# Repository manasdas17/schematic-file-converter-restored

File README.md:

**WARNING:  Upverter is in the process of overhauling our UPV format to a new version.  We don't expect to maintain the current version, however we look forward to sharing our new version with you when it's ready to go!**

The Upverter Universal Format Converter
=======================================
A command line python anything-in anything-out file converter to go between the multitude of electrical circuit schematic file formats. This project was started by Upverter (http://upverter.com).

Folder Contents
---------------

* `upconvert/core/` - All of the converter code
* `doc/` - Everything related to documentation
* `upconvert/library/` - Library files for the software packages that dont export complete files
* `upconvert/parser/` - All of the in code
* `test/` - A set of test files for each format
* `upconvert/writer/` - All of the out code

Usage
---------------

```bash
usage: python2 -m upconvert.upconverter [-h] [-i INPUT] [-f TYPE] [-o OUTPUT] [-s SYMDIRS [SYMDIRS ...]] [-t TYPE]

optional arguments:
  -h, --help            show this help message and exit

  -i INPUT, --input INPUT
                        read INPUT file in
  -f TYPE, --from TYPE  read input file as TYPE

  -o OUTPUT, --output OUTPUT
                        write OUTPUT file out
  -t TYPE, --to TYPE    write output file as TYPE

  -s SYMDIRS [SYMDIRS ...], --sym-dirs SYMDIRS [SYMDIRS ...]
                        specify SYMDIRS to search for .sym files (for gEDA
                        only)

  --unsupported         run with an unsupported python version
  --raise-errors        show tracebacks for parsing and writing errors
  --profile             collect profiling information
  -v, --version         print version information and quit
  --formats             print supported formats and quit
```

Where to Get Help
---------------

```bash
python2 -m upconvert.upconverter -h
```

  Github: Submit an issue, or pull request.
  Email: support@upverter.com

Supported Formats
---------------

  The converter can import and export in the following popular open and closed source formats.

* Upverter OpenJSON
* KiCad
* gEDA
* Fritzing
* RS274-X Gerber (see note)
* NC Drill
* Eagle
* Eagle XML             (in testing)
* ViewDraw / DxDesigner (in testing)
* DSN                   (in testing)
* PNG Image
* Bill of Materials
* CSV Netlist
* Altium                (in development)
* Telesis Netlist       (in development)

Gerber Export Note:
Gerber export requires the arial.ttf font in the working directory the converter is run from.

Format Wish List
---------------

  This is the list of formats we wish we supported, and will work on or finish someday soon. We are looking for developers to help us so please ping us if you're interested!

* OrCad
* Existing supported formats - layout data
* DipTrace

The Concept
---------------

  To use an Upverter Open JSON export in another piece of software, you will need to convert it into that software's proprietary format. Likewise, to get your data out of another piece of software and import it into Upverter, you will also need to run their export through the converter. We are working to make this easier, but we will largely depend on community contribution and the participation of the other vendors.

Interchange Format Documentation
---------------

  The converter is based on the Upverter Open JSON Format fully documented at http://support.upverter.com/customer/portal/articles/553504-documentation-for-open-json-format. We hope that someday all of the major providers of schematic capture software will support interoperability with open formats like this one.

Key Contributors
---------------

  The converter has been an ongoing project since mid-2011 made up of many, many contributions by a team of distributed developers associated by little more than our desire to fix what we see as the horribly broken world of ECAD interoperability. The key contributors are as follows:

* jdavisp3    -  KiCad, Fritzing, EagleXML, Stability
* elbaschid   -  gEDA
* iparshin    -  EagleBin
* foobarmus   -  Gerber
* patrickyeon -  ViewDraw, Image
* machinaut   -  OpenJSON, Architecture

Licence
---------------

  http://www.apache.org/licenses/LICENSE-2.0.html

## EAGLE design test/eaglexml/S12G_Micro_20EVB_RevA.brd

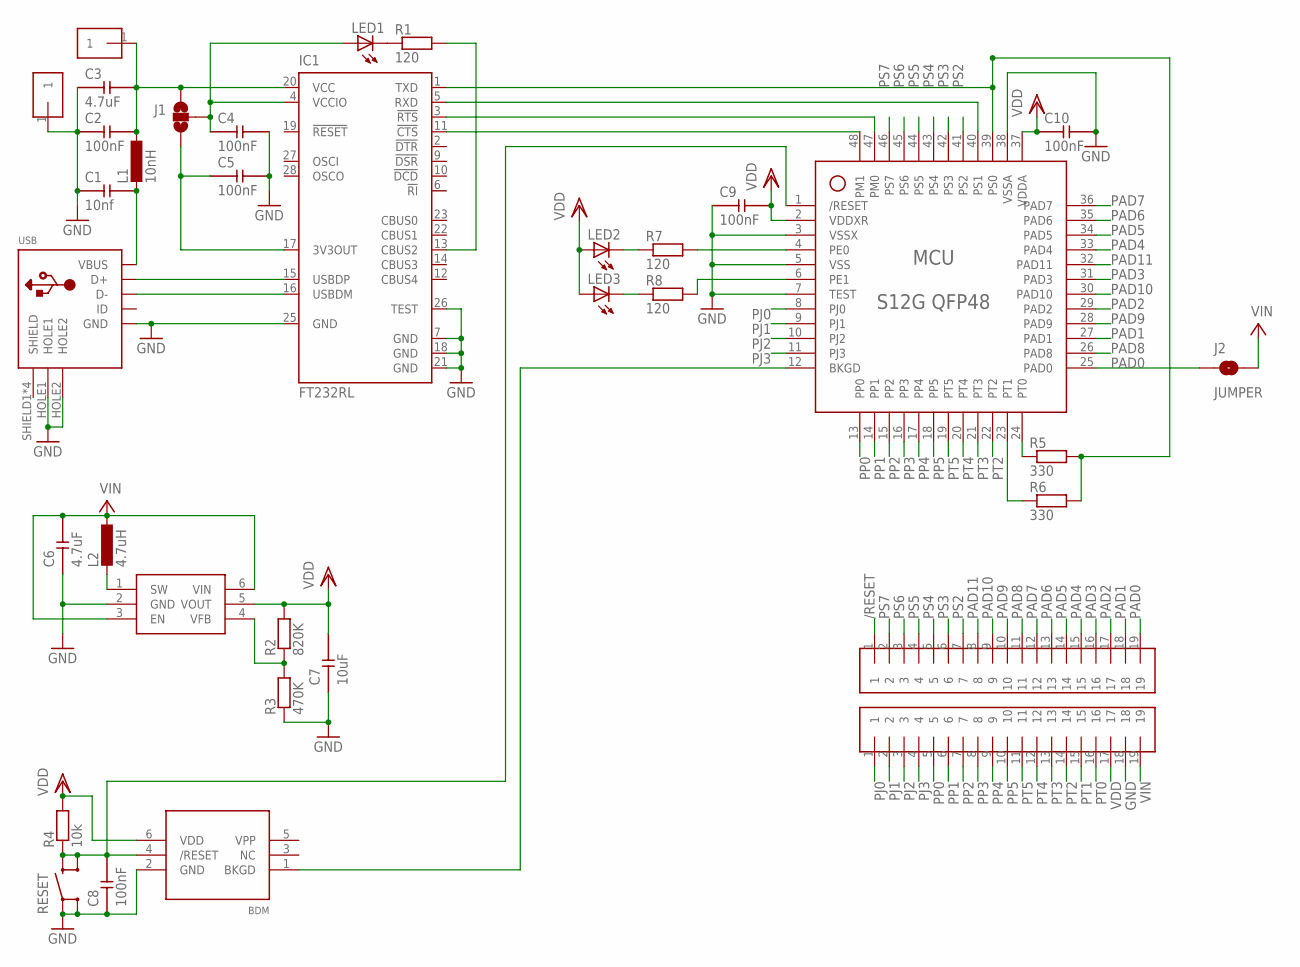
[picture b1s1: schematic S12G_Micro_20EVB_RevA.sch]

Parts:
BDM: BDM
BOTTOM: 1X19
C1: 10nf; 0805
C2, C4, C5, C8, C9, C10: 100nF; 0805
C3, C6: 4.7uF; 0805
C7: 10uF; 0805
GND: 1X1
IC1: FT232RL; SSOP28
IC2: MCP1640; SOT23-6
J1: JUMPER_2WAY
J2: JUMPER
L1: 10nH; 0805
L2: 4.7uH; LQH3C@1
LED1, LED2, LED3: LED0805; 0805
MCU: S12G QFP48; QFP44
R1, R7, R8: 120; 0805
R2: 820K; 0805
R3: 470K; 0805
R4: 10k; 0805
R5, R6: 330; 0805
RESET: BUTTON
TOP: 1X19
USB: USB; USB_MINI_B
VUSB: 1X1

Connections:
3V3OUT: C5.2, IC1.17 (3V3OUT), J1.3
/RESET: BDM.4 (/RESET), C8.1, MCU.1 (/RESET), R4.2, RESET.2, RESET.4, TOP.1
BKGD: BDM.1 (BKGD), MCU.12 (BKGD)
CTS: IC1.11 (!CTS), MCU.48 (PM1)
GND: BDM.2 (GND), BOTTOM.18, C1.2, C2.2, C3.2, C4.1, C5.1, C6.2, C7.2, C8.2, C9.2, C10.1, GND.1, IC1.7 (GND), IC1.18 (GND), IC1.21 (GND), IC1.25 (GND), IC1.26 (TEST), IC2.2 (GND), MCU.3 (VSSX), MCU.5 (VSS), MCU.7 (TEST), MCU.38 (VSSA), R3.2, RESET.1, RESET.3, USB.GND, USB.HOLE1, USB.HOLE2
unnamed: LED3.2 (C), R8.2
unnamed: IC2.4 (VFB), R2.2, R3.1
unnamed: LED2.2 (C), R7.2
unnamed: LED1.2 (C), R1.2
unnamed: IC1.13 (CBUS2), R1.1
unnamed: IC2.1 (SW), L2.3 (2), L2.4 (2)
PAD0: J2.1, MCU.25 (PAD0), TOP.19
PAD1: MCU.27 (PAD1), TOP.18
PAD2: MCU.29 (PAD2), TOP.17
PAD3: MCU.31 (PAD3), TOP.16
PAD4: MCU.33 (PAD4), TOP.15
PAD5: MCU.34 (PAD5), TOP.14
PAD6: MCU.35 (PAD6), TOP.13
PAD7: MCU.36 (PAD7), TOP.12
PAD8: MCU.26 (PAD8), TOP.11
PAD9: MCU.28 (PAD9), TOP.10
PAD10: MCU.30 (PAD10), TOP.9
PAD11: MCU.32 (PAD11), TOP.8
PE0: MCU.4 (PE0), R7.1
PE1: MCU.6 (PE1), R8.1
PJ0: BOTTOM.1, MCU.8 (PJ0)
PJ1: BOTTOM.2, MCU.9 (PJ1)
PJ2: BOTTOM.3, MCU.10 (PJ2)
PJ3: BOTTOM.4, MCU.11 (PJ3)
PP0: BOTTOM.5, MCU.13 (PP0)
PP1: BOTTOM.6, MCU.14 (PP1)
PP2: BOTTOM.7, MCU.15 (PP2)
PP3: BOTTOM.8, MCU.16 (PP3)
PP4: BOTTOM.9, MCU.17 (PP4)
PP5: BOTTOM.10, MCU.18 (PP5)
PS2: MCU.41 (PS2), TOP.7
PS3: MCU.42 (PS3), TOP.6
PS4: MCU.43 (PS4), TOP.5
PS5: MCU.44 (PS5), TOP.4
PS6: MCU.45 (PS6), TOP.3
PS7: MCU.46 (PS7), TOP.2
PT0: BOTTOM.16, MCU.24 (PT0), R5.2
PT1: BOTTOM.15, MCU.23 (PT1), R6.2
PT2: BOTTOM.14, MCU.22 (PT2)
PT3: BOTTOM.13, MCU.21 (PT3)
PT4: BOTTOM.12, MCU.20 (PT4)
PT5: BOTTOM.11, MCU.19 (PT5)
RTS: IC1.3 (!RTS), MCU.47 (PM0)
RXD: IC1.1 (TXD), MCU.39 (PS0), R5.1, R6.1
SHIELD: USB.SHIELD1 (SHIELD), USB.SHIELD2 (SHIELD), USB.SHIELD3 (SHIELD), USB.SHIELD4 (SHIELD)
TXD: IC1.5 (RXD), MCU.40 (PS1)
USBDN: IC1.16 (USBDM), USB.D-
USBDP: IC1.15 (USBDP), USB.D+
VBUS: C1.1, L1.2, USB.VBUS
VCCIO: C4.2, IC1.4 (VCCIO), J1.2, LED1.1 (A)
VDD: BDM.6 (VDD), BOTTOM.17, C7.1, C9.1, C10.2, IC2.5 (VOUT), LED2.1 (A), LED3.1 (A), MCU.2 (VDDXR), MCU.37 (VDDA), R2.1, R4.1
VDDUSB: C2.1, C3.1, IC1.20 (VCC), J1.1, L1.1, VUSB.1
VIN: BOTTOM.19, C6.1, IC2.3 (EN), IC2.6 (VIN), J2.2, L2.1, L2.5 (1)

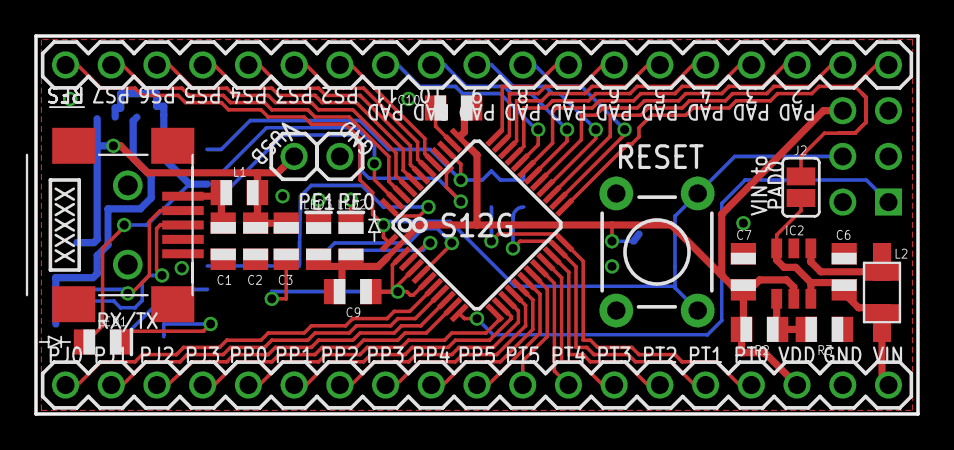
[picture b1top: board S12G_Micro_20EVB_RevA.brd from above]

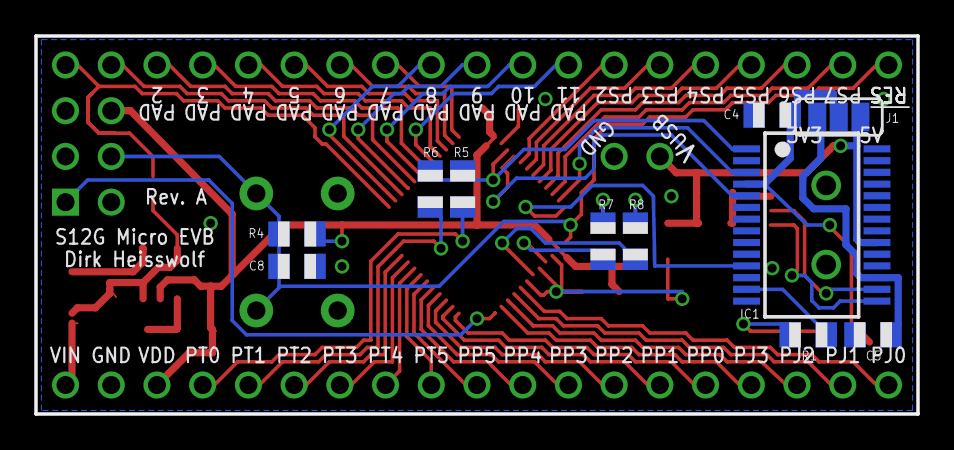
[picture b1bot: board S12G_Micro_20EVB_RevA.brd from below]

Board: 2 copper layers, 49.0 x 21.0 mm, 35 parts (11 on the bottom side), 58 nets.

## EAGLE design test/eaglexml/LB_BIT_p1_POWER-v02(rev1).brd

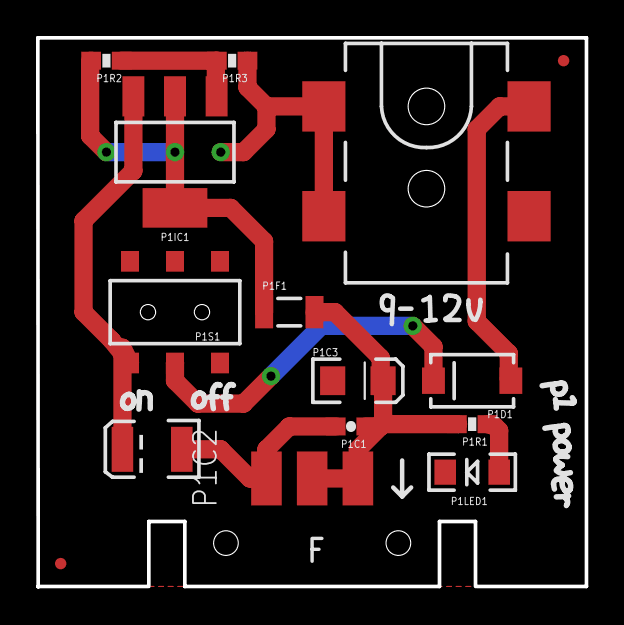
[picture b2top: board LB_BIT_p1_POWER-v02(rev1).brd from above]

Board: 2 copper layers, 30.5 x 30.5 mm, 18 parts (0 on the bottom side), 8 nets.

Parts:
JP1, JP2: FIDUCIAL1X2.5; FIDUCIAL-1X2.5
P1BSF: BITSNAP_FEMALE
P1C1: 0.1uF; 0603-CAP
P1C2: 10uF/20V; EIA3528
P1C3: 10uF; EIA3216
P1D1: MBRA140; SMA-DIODE
P1F1: 500mA PTC; PTC-1206
P1IC1: SOT223
P1J1: POWER_JACKSMD; POWER_JACK_SMD
P1LED1: RED; LED-1206
P1R1: 330; 0603-RES
P1R2: 240; 0603-RES
P1R3: 720; 0603-RES
P1S1: AYZ0202
U$1: LB_CREDITS; OSHWCREDIT
U$2: OSHW_FILLX150_NOTEXT
U$3: OSHW-LOGOL; OSHW-LOGO-L

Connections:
GND: P1BSF.GND, P1C1.2, P1C2.C, P1C3.C, P1J1.GND, P1J1.P$4, P1LED1.C, P1R3.1
unnamed: P1D1.C, P1S1.2
unnamed: P1F1.1, P1IC1.2, P1IC1.4, P1R2.2
unnamed: P1IC1.1, P1R2.1, P1R3.2
unnamed: P1C2.A, P1IC1.3, P1S1.3
unnamed: P1D1.A, P1J1.VIN0
unnamed: P1LED1.A, P1R1.1
VCC: P1BSF.SIG, P1BSF.VCC, P1C1.1, P1C3.A, P1F1.2, P1R1.2

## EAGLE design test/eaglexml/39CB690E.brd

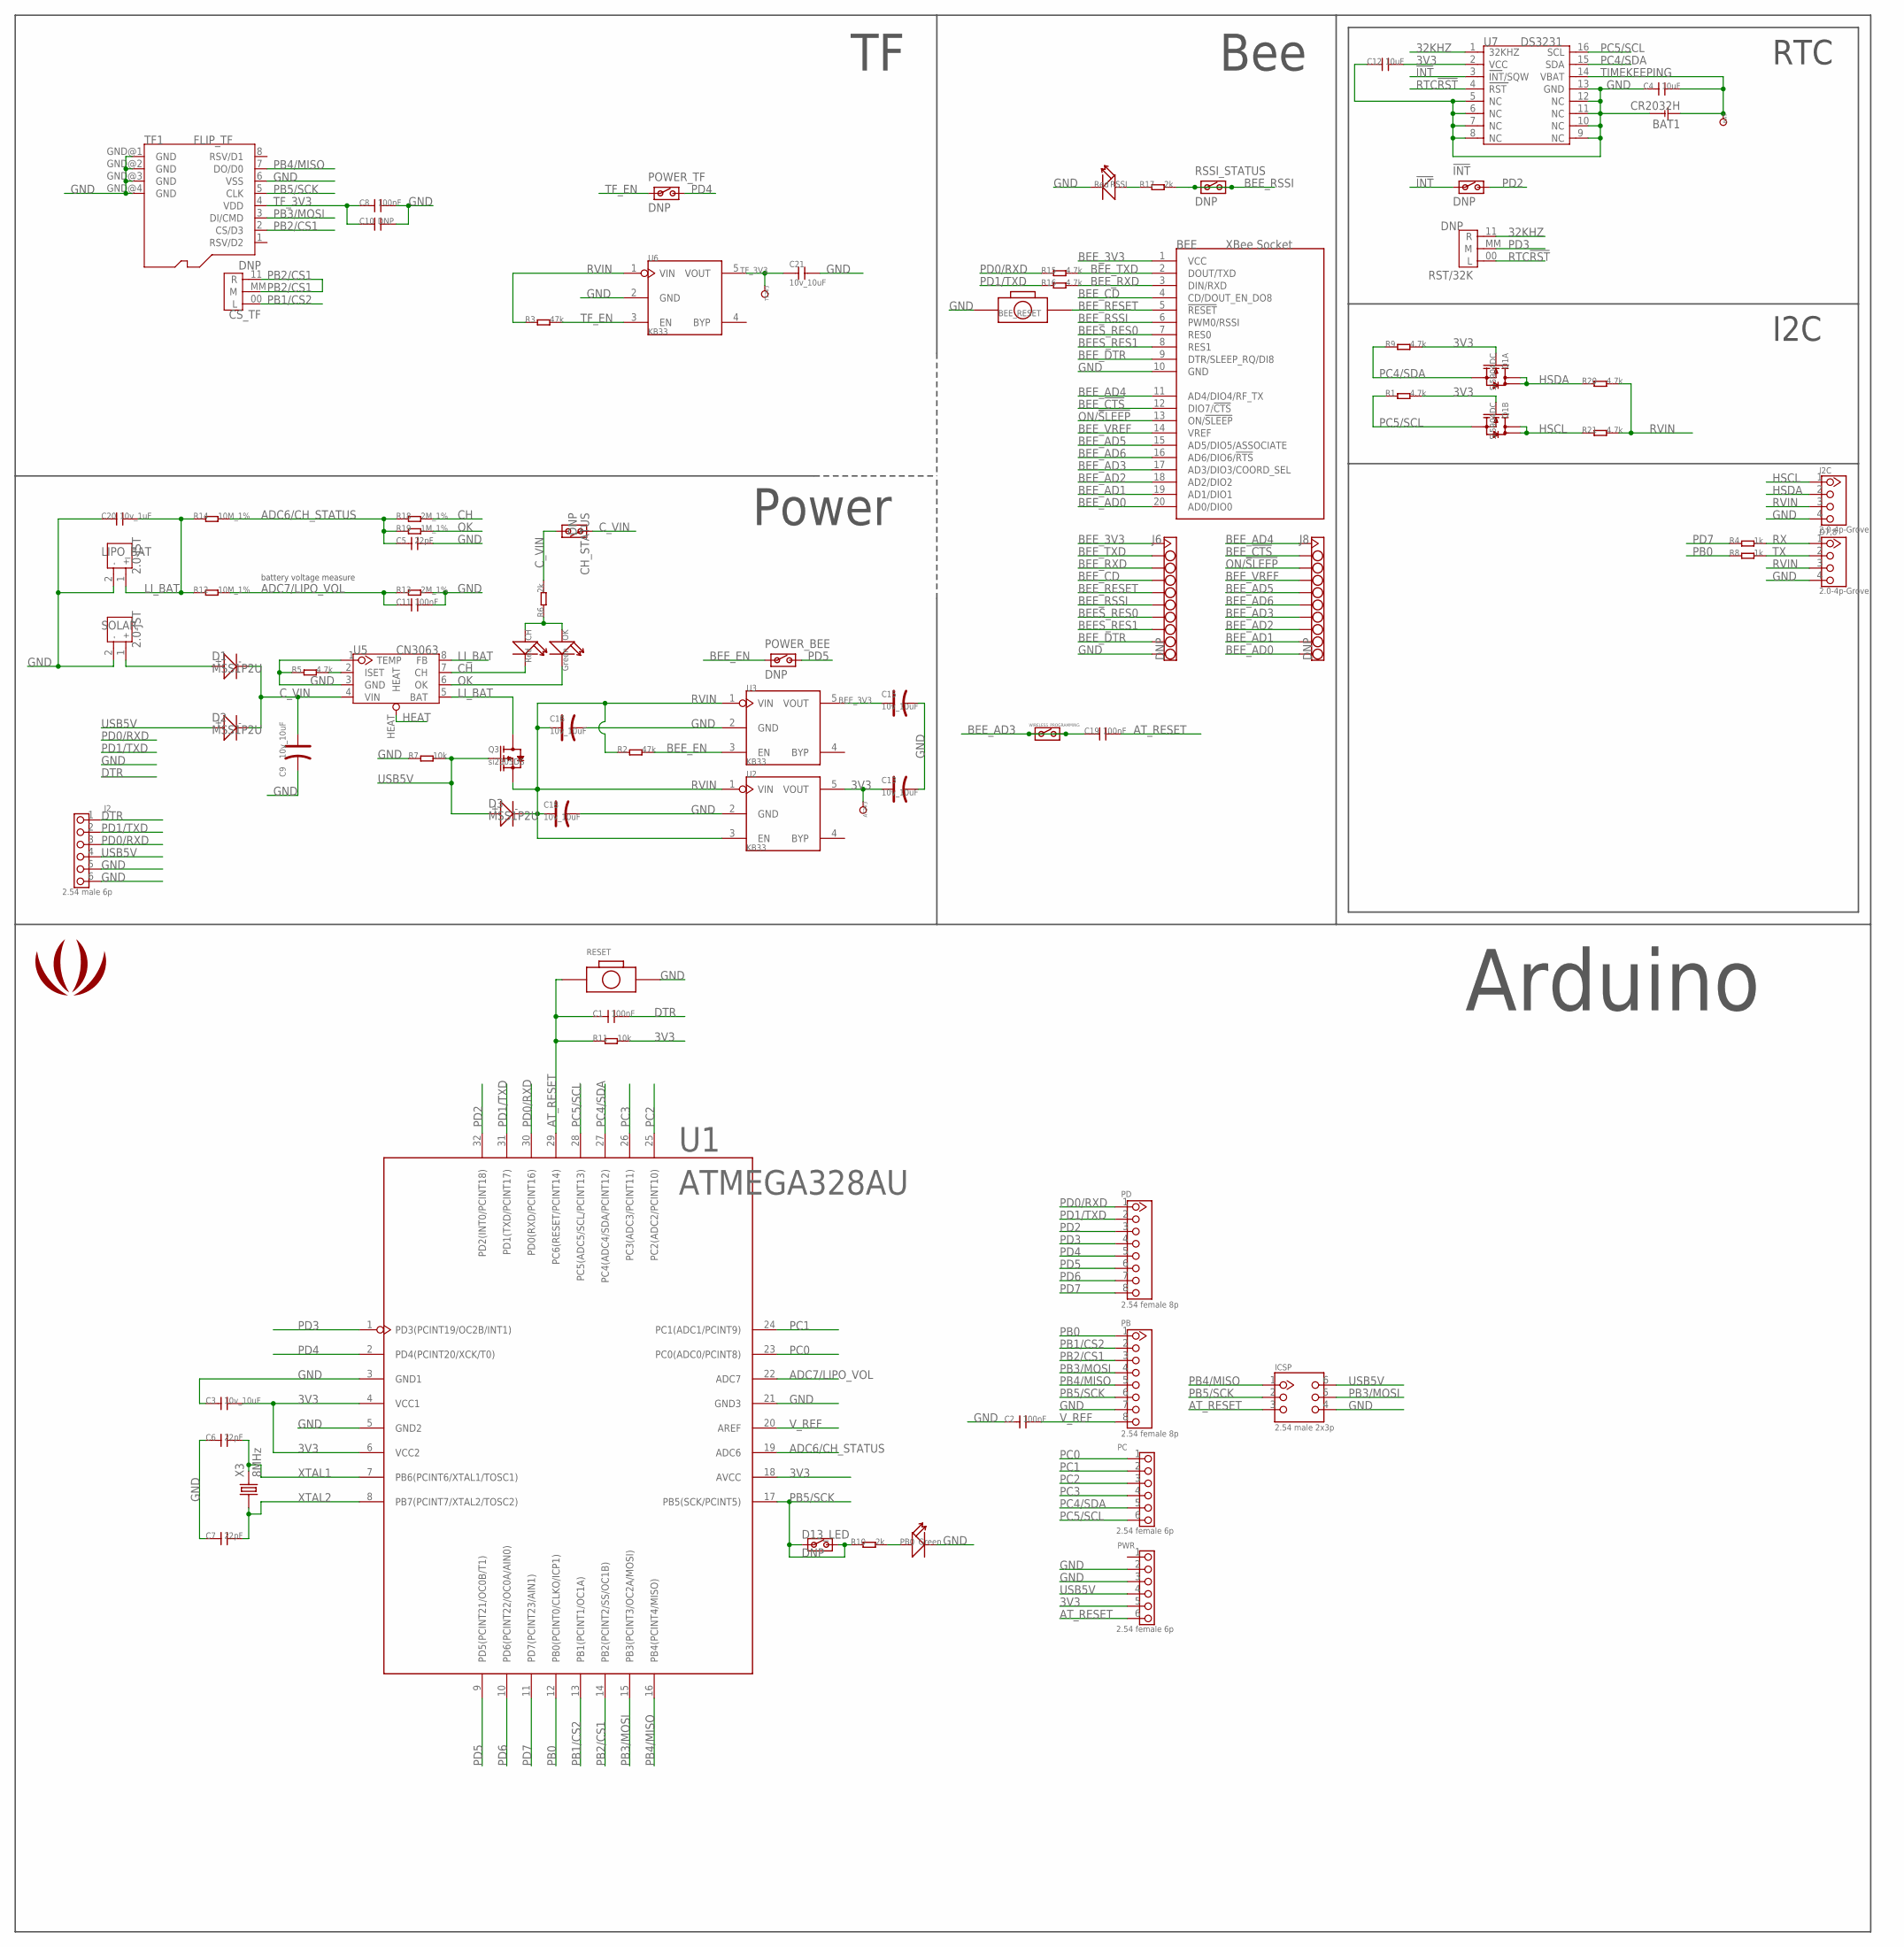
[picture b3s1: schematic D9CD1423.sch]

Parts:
!INT: DNP; JP_SW
AT3V3: DNP; TP_3535
BAT: DNP; TP_3535
BAT1: CR2032H
BEE: XBee Socket; BEE
BEE_RESET: 3.8x6.1 button; BOTTON_1
C1, C2, C8, C11, C19: 100nF; 0603
C3, C21: 10v_10uF; 0805
C4, C12: 10uF; 0805
C5, C6, C7: 22pF; 0603
C9, C13, C15, C16, C18: 10v_10uF; AVX-A
C10: DNP; 0603
C20: 10v_1uF; 0805
CH: Red; D0603
CH_STATUS: DNP; JP_SW
CS_TF: DNP; JUMPER
D1, D2, D3: MSS1P2U; D1005
D7,8: 2.0-4p-Grove; 4P-2.0
D13_LED: DNP; JP_SW
I2C: 2.0-4p-Grove; 4P-2.0
ICSP: 2.54 male 2x3p; 2X3P-2.54-LEADED
J2: 2.54 male 6p; 6P-2.54-LEADED
J6, J8: DNP; HEADER_1X10
LIPO_BAT: 2.0-JST; JST-2.0
LOGO1: LOGO; LOGO_RO
OK: Green; D0603
PB: 2.54 female 8p; 8P-2.54-LEADED
PB0: Green; D0603
PC: 2.54 female 6p; 6P-2.54-LEADED
PD: 2.54 female 8p; 8P-2.54-LEADED
POWER_BEE: DNP; JP_SW
POWER_TF: DNP; JP_SW
PWR: 2.54 female 6p; 6P-2.54-LEADED
Q1: Si5904DC; 1206-8
Q3: si2305DS; SOT23
R1, R5, R9, R15, R16, R20, R21: 4.7k; 0603@1
R2, R3: 47k; 0603@1
R4, R8: 1k; 0603@1
R6, R10, R17: 2k; 0603@1
R7, R11: 10k; 0603@1
R12, R14: 10M_1%; 0603@1
R13, R18: 2M_1%; 0603@1
R19: 1M_1%; 0603@1
RESET: 3.8x6.1 button; BOTTON_1
RSSI: Red; D0603
RSSI_STATUS: DNP; JP_SW
RST/32K: DNP; JUMPER
SOLAR: 2.0-JST; JST-2.0
TF1: FLIP_TF
TF3V3: DNP; TP_3535
U1: ATMEGA328AU; ATMEGA168-20AU
U2, U3, U6: KB33; SOT23-5
U5: CN3063; SOP8
U7: DS3231; SO16-W
WIRELESS_PROGRAMMING: DNP; JP_SW
X3: 8MHz; HC49/S

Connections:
3V3: AT3V3.T, C3.2, C12.2, C13.+, PWR.5, Q1.2 (G), Q1.4 (G), R1.2, R9.2, R11.2, U1.4 (VCC1), U1.6 (VCC2), U1.18 (AVCC), U2.5 (VOUT), U7.2 (VCC)
32KHZ: RST/32K.11 (R), U7.1 (32KHZ)
!INT: !INT.1, U7.3 (INT/SQW)
ADC6/CH_STATUS: C5.1, R14.2, R18.1, R19.1, U1.19 (ADC6)
ADC7/LIPO_VOL: C11.1, R12.2, R13.1, U1.22 (ADC7)
AT_RESET: C1.1, C19.2, ICSP.3, PWR.6, R11.1, RESET.1, U1.29 (PC6(RESET/PCINT14))
BEES_RES0: BEE.7 (RES0), J6.7
BEES_RES1: BEE.8 (RES1), J6.8
BEE_3V3: BEE.1 (VCC), C15.+, J6.1, U3.5 (VOUT)
BEE_!CTS: BEE.12 (DIO7/!CTS), J8.2
BEE_AD0: BEE.20 (AD0/DIO0), J8.10
BEE_AD1: BEE.19 (AD1/DIO1), J8.9
BEE_AD2: BEE.18 (AD2/DIO2), J8.8
BEE_AD3: BEE.17 (AD3/DIO3/COORD_SEL), C19.1, J8.7, WIRELESS_PROGRAMMING.1, WIRELESS_PROGRAMMING.2
BEE_AD4: BEE.11 (AD4/DIO4/RF_TX), J8.1
BEE_AD5: BEE.15 (AD5/DIO5/ASSOCIATE), J8.5
BEE_AD6: BEE.16 (AD6/DIO6/!RTS), J8.6
BEE_CD: BEE.4 (CD/DOUT_EN_DO8), J6.4
BEE_DTR: BEE.9 (DTR/SLEEP_RQ/DI8), J6.9
BEE_EN: POWER_BEE.1, R2.2, U3.3 (EN)
BEE_RESET: BEE.5 (!RESET), BEE_RESET.P$2 (2), J6.5
BEE_RSSI: BEE.6 (PWM0/RSSI), J6.6, R17.2, RSSI_STATUS.1, RSSI_STATUS.2
BEE_RXD: BEE.3 (DIN/RXD), J6.3, R16.2
BEE_TXD: BEE.2 (DOUT/TXD), J6.2, R15.2
BEE_VREF: BEE.14 (VREF), J8.4
CH: CH.-, R18.2, U5.7 (CH)
C_VIN: C9.+, CH_STATUS.1, CH_STATUS.2, D1.-, D2.-, R6.2, U5.4 (VIN)
DTR: C1.2, J2.1
GND: BAT1.-, BEE.10 (GND), BEE_RESET.1, C2.1, C3.1, C4.1, C5.2, C6.1, C7.1, C8.2, C9.-, C10.2, C11.2, C12.1, C13.-, C15.-, C16.-, C18.-, C20.1, C21.2, D7,8.4, I2C.4, ICSP.4, J2.5, J2.6, J6.10, LIPO_BAT.2, PB.7, PB0.-, PWR.2, PWR.3, R5.1, R7.1, R13.2, RESET.P$2 (2), RSSI.-, SOLAR.2, TF1.6 (VSS), TF1.GND@1 (GND), TF1.GND@2 (GND), TF1.GND@3 (GND), TF1.GND@4 (GND), U1.3 (GND1), U1.5 (GND2), U1.21 (GND3), U2.2 (GND), U3.2 (GND), U5.1 (TEMP), U5.3 (GND), U6.2 (GND), U7.5 (NC), U7.6 (NC), U7.7 (NC), U7.8 (NC), U7.9 (NC), U7.10 (NC), U7.11 (NC), U7.12 (NC), U7.13 (GND)
HEAT: U5.HEAT
HSCL: I2C.1, Q1.5 (D), Q1.6 (D), R21.1
HSDA: I2C.2, Q1.7 (D), Q1.8 (D), R20.1
LI_BAT: C20.2, LIPO_BAT.1, Q3.3 (D), R12.1, R14.1, U5.5 (BAT), U5.8 (FB)
unnamed: PB0.+, R10.2
unnamed: D1.+, SOLAR.1
unnamed: R5.2, U5.2 (ISET)
unnamed: R17.1, RSSI.+
unnamed: CH.+, OK.+, R6.1
OK: OK.-, R19.2, U5.6 (OK)
ON/!SLEEP: BEE.13 (ON/!SLEEP), J8.3
PB0: PB.1, R8.1, U1.12 (PB0(PCINT0/CLKO/ICP1))
PB1/CS2: CS_TF.00 (L), PB.2, U1.13 (PB1(PCINT1/OC1A))
PB2/CS1: CS_TF.11 (R), CS_TF.MM (M), PB.3, TF1.2 (CS/D3), U1.14 (PB2(PCINT2/SS/OC1B))
PB3/MOSI: ICSP.5, PB.4, TF1.3 (DI/CMD), U1.15 (PB3(PCINT3/OC2A/MOSI))
PB4/MISO: ICSP.1, PB.5, TF1.7 (DO/D0), U1.16 (PB4(PCINT4/MISO))
PB5/SCK: D13_LED.1, D13_LED.2, ICSP.2, PB.6, R10.1, TF1.5 (CLK), U1.17 (PB5(SCK/PCINT5))
PC0: PC.1, U1.23 (PC0(ADC0/PCINT8))
PC1: PC.2, U1.24 (PC1(ADC1/PCINT9))
PC2: PC.3, U1.25 (PC2(ADC2/PCINT10))
PC3: PC.4, U1.26 (PC3(ADC3/PCINT11))
PC4/SDA: PC.5, Q1.1 (S), R9.1, U1.27 (PC4(ADC4/SDA/PCINT12)), U7.15 (SDA)
PC5/SCL: PC.6, Q1.3 (S), R1.1, U1.28 (PC5(ADC5/SCL/PCINT13)), U7.16 (SCL)
PD0/RXD: J2.3, PD.1, R15.1, U1.30 (PD0(RXD/PCINT16))
PD1/TXD: J2.2, PD.2, R16.1, U1.31 (PD1(TXD/PCINT17))
PD2: !INT.2, PD.3, U1.32 (PD2(INT0/PCINT18))
PD3: PD.4, RST/32K.MM (M), U1.1 (PD3(PCINT19/OC2B/INT1))
PD4: PD.5, POWER_TF.2, U1.2 (PD4(PCINT20/XCK/T0))
PD5: PD.6, POWER_BEE.2, U1.9 (PD5(PCINT21/OC0B/T1))
PD6: PD.7, U1.10 (PD6(PCINT22/OC0A/AIN0))
PD7: PD.8, R4.1, U1.11 (PD7(PCINT23/AIN1))
RTC!RST: RST/32K.00 (L), U7.4 (RST)
RVIN: C16.+, C18.+, D3.-, D7,8.3, I2C.3, Q3.2 (S), R2.1, R3.1, R20.2, R21.2, U2.1 (VIN), U2.3 (EN), U3.1 (VIN), U6.1 (VIN)
RX: D7,8.1, R4.2
TF_3V3: C8.1, C10.1, C21.1, TF1.4 (VDD), TF3V3.T, U6.5 (VOUT)
TF_EN: POWER_TF.1, R3.2, U6.3 (EN)
TIMEKEEPING: BAT.T, BAT1.+, C4.2, U7.14 (VBAT)
TX: D7,8.2, R8.2
USB5V: D2.+, D3.+, ICSP.6, J2.4, PWR.4, Q3.1 (G), R7.2
V_REF: C2.2, PB.8, U1.20 (AREF)
XTAL1: C6.2, U1.7 (PB6(PCINT6/XTAL1/TOSC1)), X3.2
XTAL2: C7.2, U1.8 (PB7(PCINT7/XTAL2/TOSC2)), X3.1

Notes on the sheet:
Power
Arduino
Bee
battery voltage measure
RTC
I2C

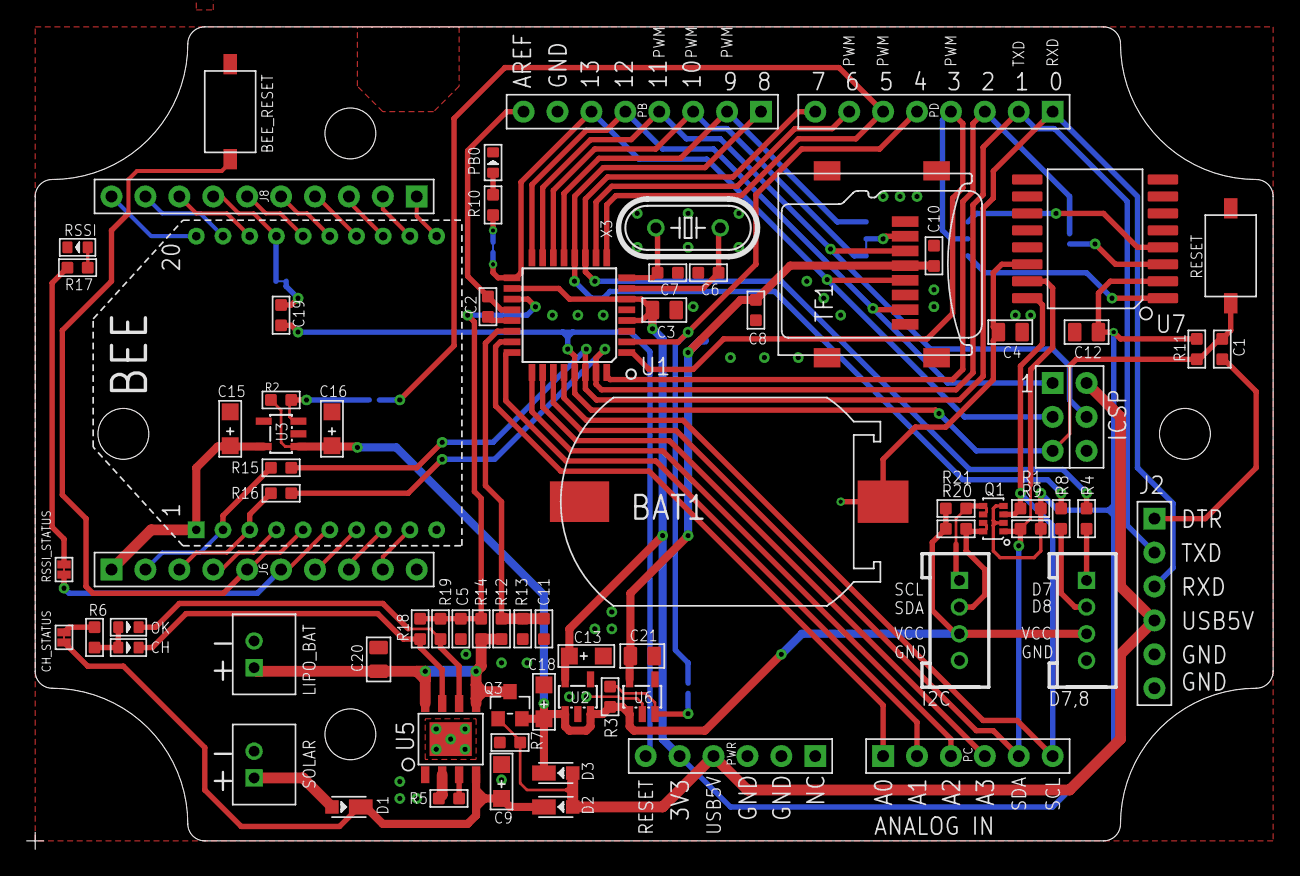
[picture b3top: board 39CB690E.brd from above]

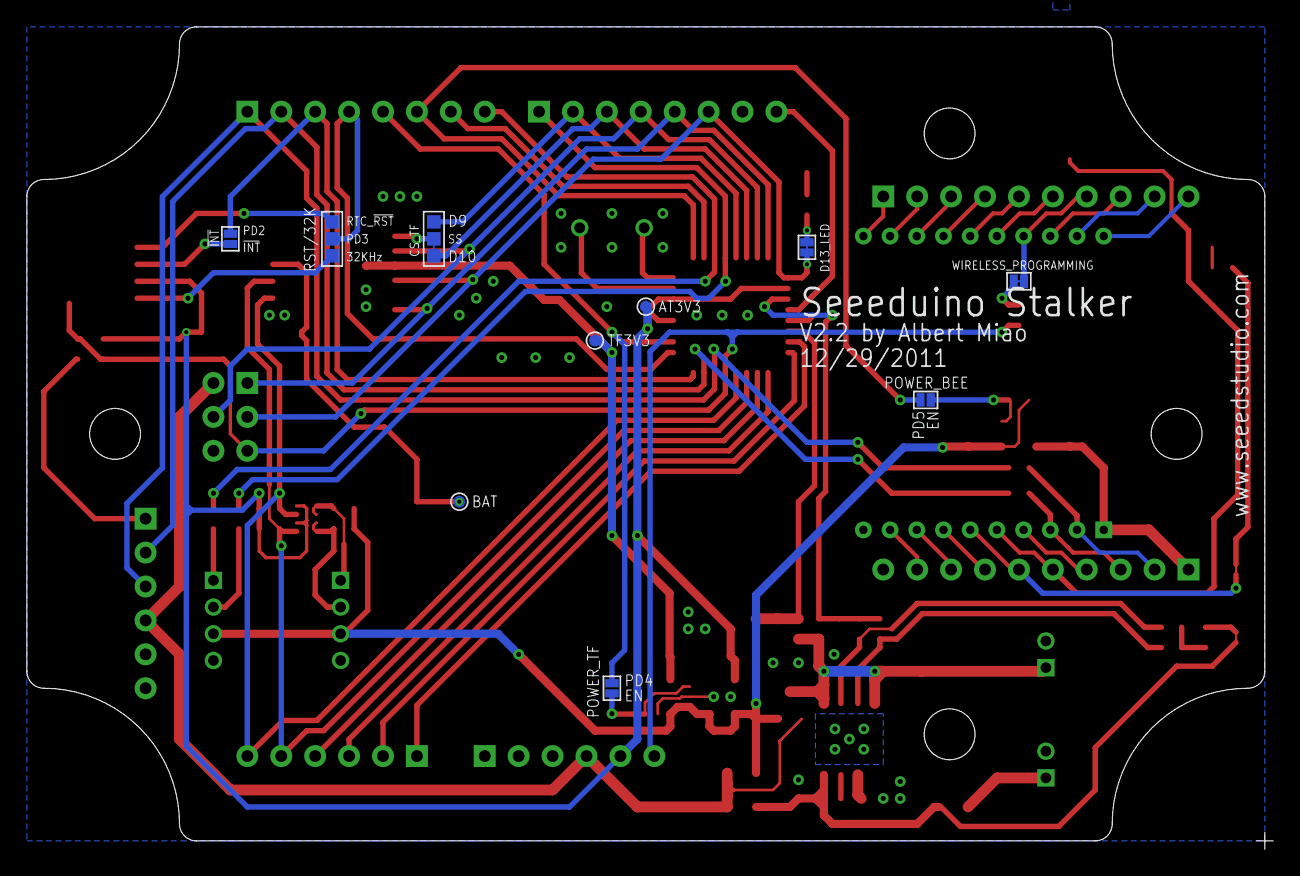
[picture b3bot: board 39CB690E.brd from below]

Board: 2 copper layers, 93.3 x 61.6 mm, 86 parts (10 on the bottom side), 70 nets.

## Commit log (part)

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2012-06-06 adding attribute stringification
2012-06-06 minor bug
2012-06-07 hard coded the component instance symbol index to 0
2012-06-07 Please run on Python 2.7!
2012-06-07 Initial .dsn file parser
2012-06-07 changed vertion to 0.3
2012-06-08 adding scaling functions to the core
2012-06-08 changed eagle annotations to be reletive and corrected annotation and designs scaling
2012-06-08 bug not scaling labels
2012-06-08 fixing scaling issue with pins
2012-06-08 Handle fzz files with wrong extension in auto-detect.
2012-06-09 Tweak fritzing part search. Add library for 0.7.4b.
2012-06-10 Refactored sub-node parsing into its own method
2012-06-10 Roughed-in ViewDraw file auto-detect.
2012-06-11 updating the format support
2012-06-11 Implementing specctra design language...
2012-06-11 More DSN objects...
2012-06-12 Conversion to upconvert format
2012-06-13 Whitespace.
2012-06-13 Eagle XML rectangles and pins, plus start of nets.
2012-06-13 eagle parser polishing: better text rotations, polygons to openjson conversion
2012-06-14 More appropriate assertion methods
2012-06-14 added init files the the new fritzing lib dirs
2012-06-15 Pyflakes fix.
2012-06-15 Work on eaglexml components and nets.
2012-06-16 minor whitespace cleanup
2012-06-16 removed 'cond and s1 or s2' style statements
2012-06-16 shutting pylint up for good
2012-06-18 Working on conversion
2012-06-20 pin connections
2012-06-20 pins and shape rotation
2012-06-21 Parse partially quoted strings, workaround for undocumented(?) parameter in pins descriptor
2012-06-22 fixing float json export to int
2012-06-22 Initial stubs for Specctra DSN support
2012-06-22 revert "Please run on Python 2.7!"
2012-06-26 fix arc tests after changing arc parsing to line up with spec
2012-06-26 Remove temp file.
2012-06-26 Start eaglexml writer.
2012-06-26 adding a version arg
2012-06-26 tweaking version to use a hard coded tag number
2012-06-26 minor updates to the readme
2012-06-26 cleanup to the versioning stuff
2012-06-27 import & export
2012-06-27 fix rotation issues and turn off wiring
2012-06-28 Fix spelling.
2012-06-28 Work on eaglexml writing.
2012-06-28 Can't get qarc working at freerouting.net, draw it using lines
2012-06-28 bezier curves
2012-06-29 One openjson component for one logical eaglexml part.
2012-06-29 flip attribute
2012-07-01 Minor shape glitches
2012-07-02 Streamlining by removing extraneous arguments
2012-07-02 better flow to the code
2012-07-03 Colouring styles for rendered images
2012-07-03 Work on eaglexml output.
2012-07-03 added flip
2012-07-04 flipped components drawn properly
2012-07-04 symbols can be flipped now, so viewdraw uses that
2012-07-06 moving strigify into utils
2012-07-06 test fix
2012-07-07 image generation working
2012-07-07 fixing bugs with optional image support
2012-07-07 adding a format support information option
2012-07-10 fixing a bug in geda parser
2012-07-10 Generate eaglexml segment pinrefs.
2012-07-10 fixed most of the scons test errors
2012-07-11 Eaglexml output tests.
2012-07-12 added more test cases, caught more errors
2012-07-12 fixed test a bit more
2012-07-13 Handle eaglexml polygons.
2012-07-15 Image output fix (scaling, style)
    I see now that there was a protocol in place for writers, so the Image
    writer is being brought into line (mostly the .write(design, filename)
    calling convention.
    I've removed dependence on having the design do any conversions, it
    does not seem like a good idea to me. For one, it seems appropriate for
    the writer to wholly take on that responsibility, no reason that
2012-07-15 Refactoring inside image.py
    I'm aiming to have better division of responsibility/ownership for the
    image writer. To this end, there is now a Worker class that does all the
    drawing work. It encapsulates the design and canvas to be rendered to
    (streamlining the arguments when calling the draw_ methods), while the
    original Image class holds details about the output format. This will
    allow eg. having one Image instance for each style of rendered output
2012-07-15 bugfix for scaled images
2012-07-15 Update todos.
2012-07-15 Handle polygon output.
2012-07-16 removed folder
2012-07-16 removing empty upv test files
2012-07-16 removing 2 more empty upv files
2012-07-16 oops
2012-07-16 updating scons lint
2012-07-16 fixing git ignore to ignore out-simple
2012-07-16 adding some eagle xml files
2012-07-17 Support eaglexml circles.
2012-07-17 scons linter fixes
2012-07-17 geda symbols load
2012-07-19 Rotations used in a few more places
2012-07-19 updating tests because of more rotations
2012-07-22 fixed instance ID generation to create unique IDs
2012-07-24 Actually draw rounded rectangles
2012-07-24 Eaglexml layer output.
2012-07-24 Scaled components work from ViewDraw
    Components that are instantiated in a ViewDraw design with some scaling
    now have a scaled copy added to the component library and that is used
    instead.
2012-07-24 library files read in with geda and kicad. support for filepicker integration
2012-07-24 fixed rotation error causing design to not load properly
2012-07-25 fixed rounding error with rotation
2012-07-26 removed geda test files
2012-07-26 geda library files in same folder as input file will be read
2012-07-27 Fix kicad test.
2012-07-27 Pin visibility and direction.
2012-07-27 spelling error
2012-07-28 Combine overlapping nets together.
2012-07-31 Fix test.
2012-08-01 drawing arcs no longer a special case
    Thanks to Shape.Arc.ends, no longer need to special-case passing along
    the rotation when drawing an arc. Now all the shapes have the same
    calling convention.
2012-08-01 re-adding instance rotations
2012-08-02 Fix docstring.
2012-08-02 Scale design attributes.
2012-08-02 round pins to multiples of 10s
2012-08-02 round pins to 10 for geda
2012-08-03 fixed pin rounding to just round the ends
2012-08-03 removed pin rounding
2012-08-04 added lightning project for GEDA testing
2012-08-04 updated lightning test project
2012-08-04 added test for lightning test project and fixed connected components
2012-08-05 fixed error with loading schema in current directory
2012-08-05 fixed up geda parser according to flake8
2012-08-05 cleaned up code with pylint
2012-08-05 adding more eaglexml test files
2012-08-07 moved kicad test project to own directory inside test/kicad
2012-08-07 geda symbol lookup is now case insensitive
2012-08-07 fixed path for test file since it's been moved. also fixed indentation error
2012-08-07 added docstrings at the top of the file in addition to the function
2012-08-08 Fix tests.
2012-08-09 Create single-point nets for overlapping pins. (Only pins not already in other nets).
2012-08-09 Fix pin length generation.
2012-08-09 Fix duplicate net problem.
2012-08-10 export kicad projects as .zip. fixed component names in lib file to match with .sch file
2012-08-10 export geda as a zip of symbols and schematic files
2012-08-13 eagle xml writer - fixed component naming, added pin names.
2012-08-14 Fix geda tests.
2012-08-14 eaglexml export. write unique pin names
2012-08-15 Create single-point nets for overlapping pins.
2012-08-15 eagle xml writer. elongate pin lengths so they dont overlap on import. change net points accordingly
2012-08-16 added flip support to the kicad parser+writer
2012-08-16 kicad parser. fix duplicate instance ids
2012-08-16 added mult scale to kicad tests, removed exported text file from geda test
2012-08-21 adding more specctra test files
2012-08-21 refactoring for layout
2012-08-21 updating test.py to run cleaner
2012-08-21 fixing image writer to handle both schematics and layouts
2012-10-05 add repr to shape.Line to help debugging
2012-10-05 fix missing self in component_instance for side
2012-10-06 add trace_segment and layer_options to openjson parser
2012-10-06 remove Layout.generate_netlist and Layout.get_trace
2012-10-06 add Segment class to core.layout
2012-10-06 add repr for component instance
2012-10-11 convert units from the core (nm) into the current gerber's units
2012-10-13 add rotate methods to Point, Label, Line, Circle classes
2012-10-13 add add_shape method to gerber layout.Image class, does relative rotation, flip positioning
2012-10-13 write component footprint instance bodies to gerber file using Image.add_shape
2012-10-15 add __repr__ to GenObjAttribute
2012-10-15 add Via and PlatedThroughHole generated object bodies methods
2012-10-15 add repr method to Circle
2012-10-15 add Circle and Rectangle to Image.add_shape
2012-10-16 add Macro, MacroAperture classes, remove un-necessary json shape methods. add equality methods
2012-10-16 define macros from complex instances when building images
2012-10-16 tighten silkscreen line width to 015mm (from 0.25)
2012-10-16 convert units on regular polygon verticies
2012-10-17 gerber processing design level generated objects
2012-10-17 remove rotate debugging logging for generated objects
2012-10-19 add body generation for padstacks
2012-10-19 add font size and font family to label shape
2012-10-19 WIP render text in gerbers as outlines
2012-10-24 rotate, move, caching of points and bounding boxes for labels
2012-10-24 use centered rectangle in generated objects
2012-10-24 zero out position for design layout objects, positioning has already been acounted for in body generation
2012-10-25 parse footprint_pos rotation as boolean
2012-10-25 Add flip methods to shapes
2012-10-26 center rectangles on pad stacks
2012-10-26 only update label _rotation when no segments have been rendered
2012-10-29 include mechanical details for board outline design attributes
2012-10-29 add writer for ncdrill files
2012-11-02 include font_family and font_size in json label export
2012-11-02 add Path class in generated_object
2012-11-02 parse shapes from openjson format
2012-11-02 draw lines for paths in gerber output
2012-11-02 bump version in vrsn from 0.6.1 to 0.7.0
2012-11-02 leave layer type out of gerber conf file
2012-11-06 add missing footprint_json in call to parse json in openjson
2012-11-14 adding diptrace to the readme
2012-11-18 Apply rotations to eaglexml rectangles.
2012-11-21 Handle curves on wires. Fix bug in net point calculation.
2012-11-23 Tweak pin label positioning.
2012-11-23 Add gate name for multi-gate parts to >NAME annotations.
2012-11-28 >NAME and >VALUE are case insensitive.
2012-12-05 move freetype initialization into gerber writer, don't render bitmaps on load_char
2012-12-06 add note to README.md about arial.ttf dependency for gerber export
2012-12-07 Fix spelling in docstring.
2012-12-08 label.(_)rotation fix for viewdraw.py
2012-12-08 fix in image.py for design.traces rename
2012-12-08 Fix smashed annotations positioning.
2013-01-08 fix flip -> flip_horizontal use in component_instance
2013-01-08 update shape rotate to modify shape.rotation in favor or modifying shape parameters
2013-01-08 use shape rotation when creating aperture macros
2013-01-11 add Pour class to generated_object file
2013-01-11 parse pours from the openjson format into the core
2013-01-14 fix flip -> flip_horizontal on FootprintAttribute
2013-01-14 fix apture naming for rectangles with rotations
2013-01-14 parse rotate and flip_horizontal for pour shapes
2013-01-14 rev version to 0.8.0
2013-01-15 fix flip -> flip_horizontal, bump version 0.8.1
2013-01-27 include label in annotations
2013-01-27 write board level text to the gerber
2013-01-27 rev version to v0.8.2
2013-01-28 fix flip -> flip_horizontal in ncdrill export
2013-01-29 extract footprint variant index in the openjson parser
2013-02-11 skip ncdrill non-circular holes
2013-02-12 do flip 'inplace' on rectangles on openjson parse
2013-03-11 corrected leading zero commands to correct units
2013-03-12 include flip, rotation on FBody class to match FLBs
2013-03-13 rev version to 0.8.7
2013-03-16 rev version number to 0.8.8
2013-04-13 updates for flipped rectangle
2013-12-03 fix Undefined variable 'p'
2013-12-04 fix linter err in eagle parser, raw string r'\0'
2013-12-04 removed unused argument 'design'. put back in if intend to use(?).

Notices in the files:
parts and their libraries:
LITTLEBITS: Released under the Creative Commons Attribution Share-Alike 3.0 License
LITTLEBITS: http://creativecommons.org/license/by-sa/3.0
